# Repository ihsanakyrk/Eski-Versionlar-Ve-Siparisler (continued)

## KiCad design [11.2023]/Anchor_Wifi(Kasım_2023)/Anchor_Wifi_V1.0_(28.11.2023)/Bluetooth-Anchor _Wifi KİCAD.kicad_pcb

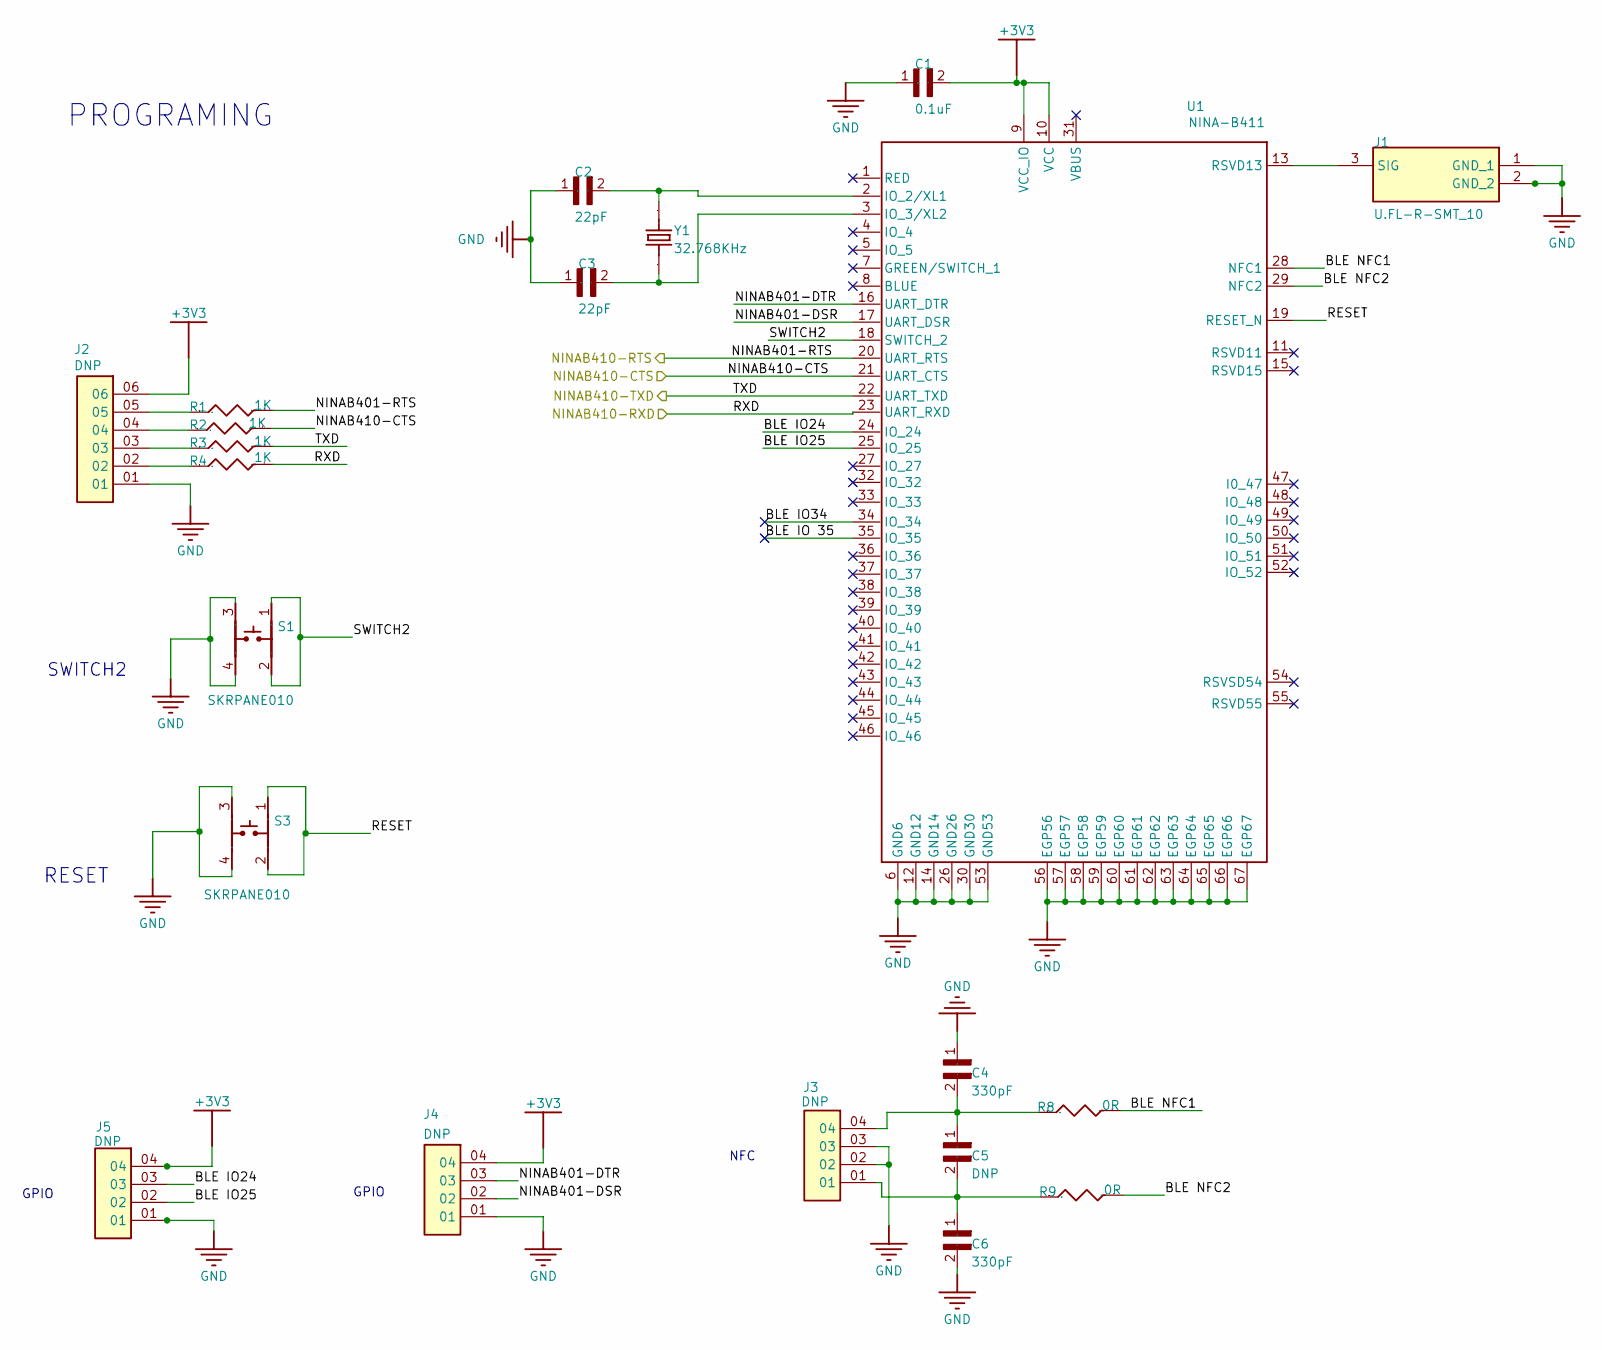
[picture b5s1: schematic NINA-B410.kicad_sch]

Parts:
C1: 0.1uF; C_0402
C2, C3: 22pF; C_0402
C4, C6: 330pF; C_0402
C5: DNP; C_0402
J1: U.FL-R-SMT_10; UFLRSMT10; MANUFACTURER_PART_NUMBER U.FL-R-SMT(10); MOUSER PART NUMBER 798-U.FL-R-SMT10
J2: DNP; Header_6Ways_2x54
J3, J4, J5: DNP; Header_4Ways_2x54_Male
R1, R2, R3, R4: 1K; Res_0402
R8, R9: 0R; Res_0402
S1, S3: SKRPANE010
U1: NINA-B411; NINA_LGA67R_1160X1000X223_PIN - duplicate
Y1: 32.768KHz; XTAL_ECS-3X8X

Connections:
+3V3: C1.2, J2.06, J4.04, J5.04, U1.9 (VCC_IO), U1.10 (VCC); also elsewhere on the board
BLE IO24: J5.03, U1.24 (IO_24)
BLE IO25: J5.02, U1.25 (IO_25)
BLE IO34: U1.34 (IO_34)
BLE IO 35: U1.35 (IO_35)
BLE NFC1: R8.2, U1.28 (NFC1)
BLE NFC2: R9.2, U1.29 (NFC2)
GND: C1.1, C2.1, C3.1, C4.1, C6.2, J1.1 (GND_1), J1.2 (GND_2), J2.01, J3.02, J3.03, J4.01, J5.01, S1.3, S1.4, S3.3, S3.4, U1.6 (GND6), U1.12 (GND12), U1.14 (GND14), U1.26 (GND26), U1.30 (GND30), U1.53 (GND53), U1.56 (EGP56), U1.57 (EGP57), U1.58 (EGP58), U1.59 (EGP59), U1.60 (EGP60), U1.61 (EGP61), U1.62 (EGP62), U1.63 (EGP63), U1.64 (EGP64), U1.65 (EGP65), U1.66 (EGP66), U1.67 (EGP67); also elsewhere on the board
NINAB401-DSR: J4.02, U1.17 (UART_DSR)
NINAB401-DTR: J4.03, U1.16 (UART_DTR)
NINAB401-RTS: R1.2, U1.20 (UART_RTS); also elsewhere on the board
NINAB410-CTS: R2.2, U1.21 (UART_CTS); also elsewhere on the board
NetC2_2: C2.2, U1.2 (IO_2/XL1), Y1.2
NetC3_2: C3.2, U1.3 (IO_3/XL2), Y1.1
NetC4_2: C4.2, C5.1, J3.04, R8.1
NetC6_1: C5.2, C6.1, J3.01, R9.1
NetJ1_3: J1.3 (SIG), U1.13 (RSVD13)
NetJ2_02: J2.02, R4.1
NetJ2_03: J2.03, R3.1
NetJ2_04: J2.04, R2.1
NetJ2_05: J2.05, R1.1
RESET: S3.1, S3.2, U1.19 (RESET_N)
RXD: R4.2, U1.23 (UART_RXD); also elsewhere on the board
SWITCH2: S1.1, S1.2, U1.18 (SWITCH_2)
TXD: R3.2, U1.22 (UART_TXD); also elsewhere on the board

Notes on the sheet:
GPIO
RESET
NFC
SWITCH2
PROGRAMING

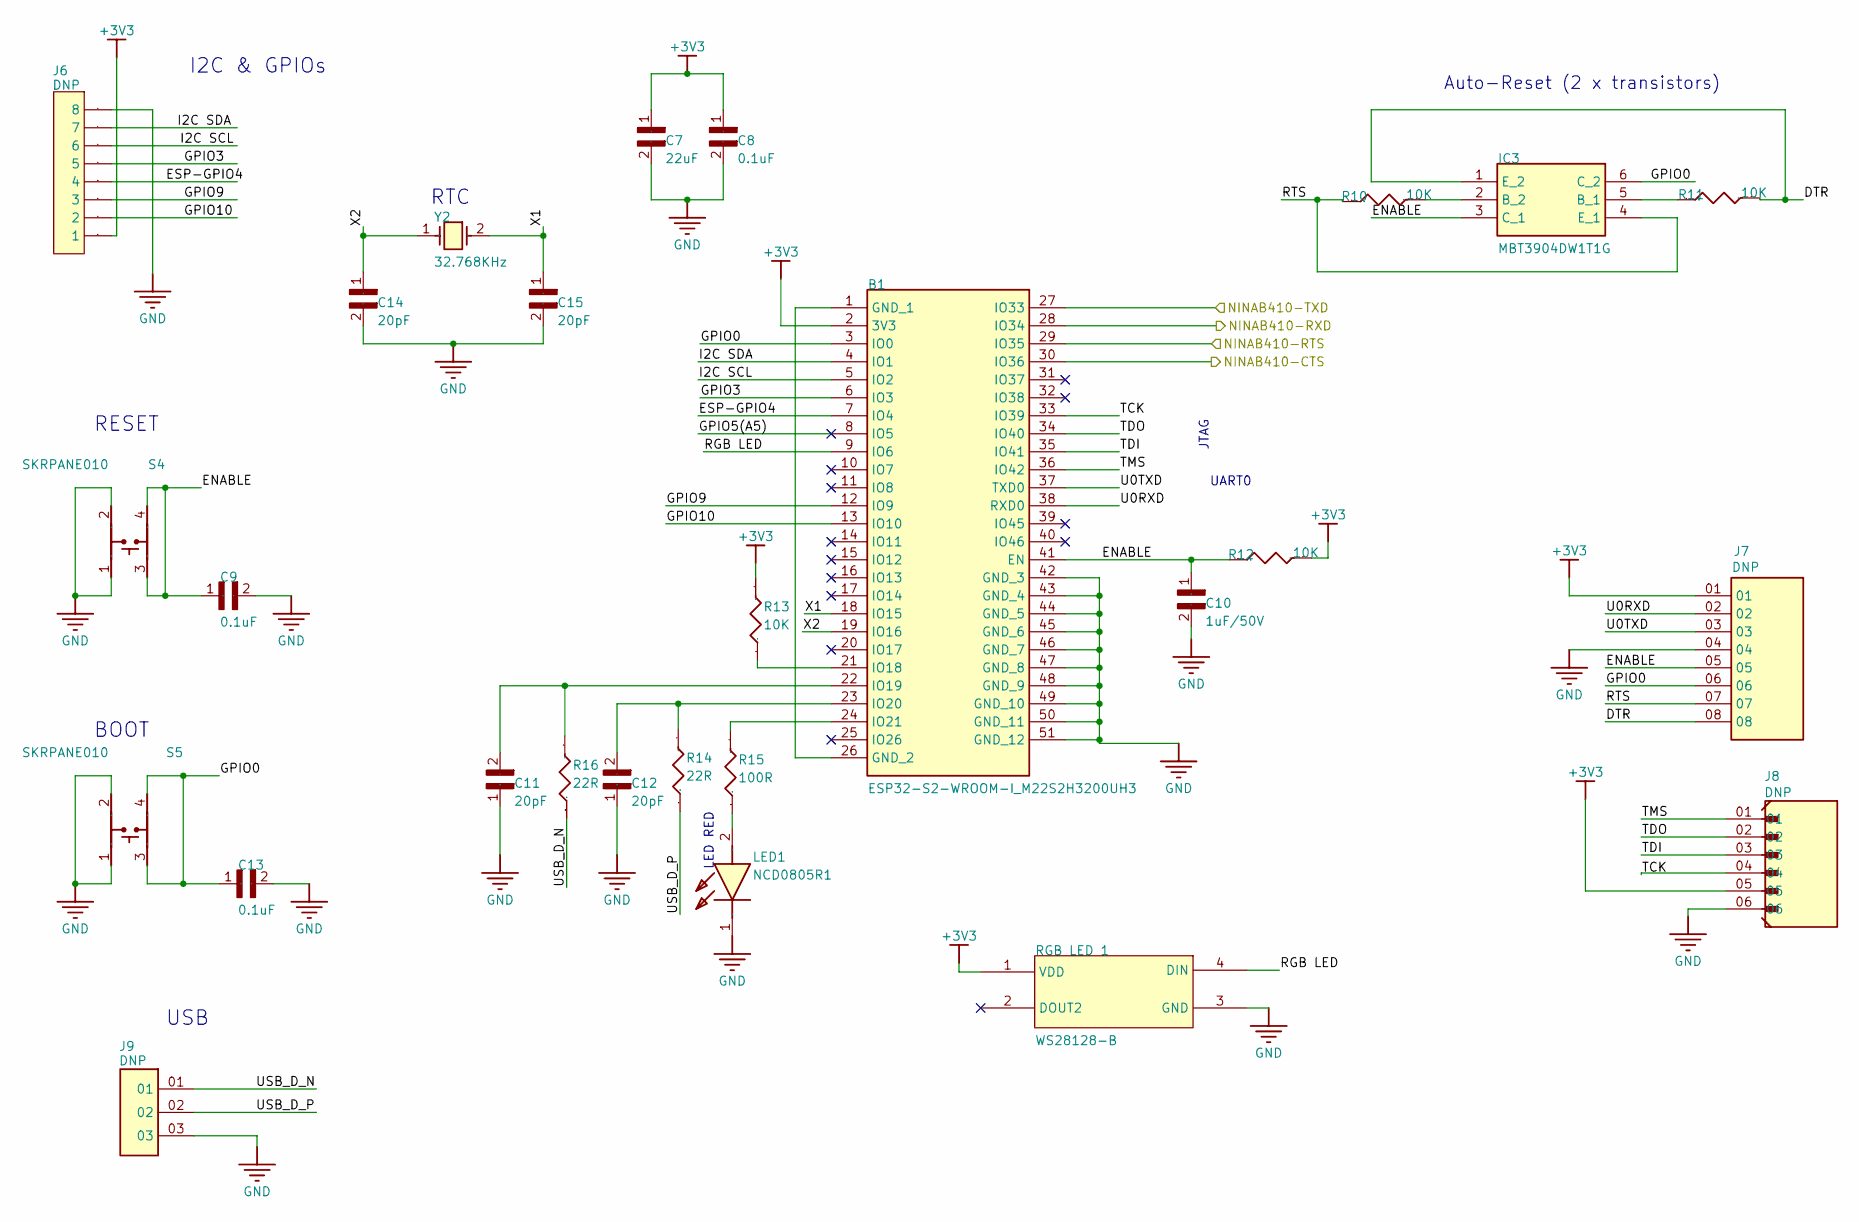
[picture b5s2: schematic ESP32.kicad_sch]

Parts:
B1: ESP32-S2-WROOM-I_M22S2H3200UH3; ESP32S2WROOMIM22S2H3200UH3Q0; MANUFACTURER_PART_NUMBER ESP32-S2-WROOM-I(M22S2H3200UH3Q0); MOUSER PART NUMBER 356-ESP32S2WRMI320UH
C7: 22uF; C_0402
C8, C9, C13: 0.1uF; C_0402
C10: 1uF/50V; C_0402
C11, C12, C14, C15: 20pF; C_0402
IC3: MBT3904DW1T1G; MANUFACTURER_PART_NUMBER MBT3904DW1T1G; MOUSER PART NUMBER 863-MBT3904DW1T1G
J6: DNP; Header_8ways_2x54
J7: DNP; 2x54 Header 8 pin
J8: DNP; Header_1x6_2_54
J9: DNP; Header_3Ways_2x54
LED1: NCD0805R1; MANUFACTURER_PART_NUMBER NCD0805R1; MOUSER PART NUMBER *
R10, R11, R12, R13: 10K; Res_0402
R14, R16: 22R; Res_0402
R15: 100R; Res_0402
RGB LED 1: WS28128-B
S4, S5: SKRPANE010
Y2: 32.768KHz; XTAL_ECS-3X8X

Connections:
+3V3: B1.2 (3V3), C7.1, C8.1, J6.1, J7.01, J8.05, R12.2, R13.2, RGB LED 1.1 (VDD); also elsewhere on the board
DTR: IC3.1 (E_2), J7.08, R11.2
ENABLE: B1.41 (EN), C9.1, C10.1, IC3.3 (C_1), J7.05, R12.1, S4.3, S4.4
ESP-GPIO4: B1.7 (IO4), J6.4
GND: B1.42 (GND_3), B1.43 (GND_4), B1.44 (GND_5), B1.45 (GND_6), B1.46 (GND_7), B1.47 (GND_8), B1.48 (GND_9), B1.49 (GND_10), B1.50 (GND_11), B1.51 (GND_12), C7.2, C8.2, C9.2, C10.2, C11.1, C12.1, C13.2, C14.2, C15.2, J6.8, J7.04, J8.06, J9.03, LED1.1 (K), RGB LED 1.3 (GND), S4.1, S4.2, S5.1, S5.2; also elsewhere on the board
GPIO0: B1.3 (IO0), C13.1, IC3.6 (C_2), J7.06, S5.3, S5.4
GPIO3: B1.6 (IO3), J6.5
GPIO5(A5): B1.8 (IO5)
GPIO9: B1.12 (IO9), J6.3
GPIO10: B1.13 (IO10), J6.2
I2C SCL: B1.5 (IO2), J6.6
I2C SDA: B1.4 (IO1), J6.7
NINAB401-RTS: B1.29 (IO35); also elsewhere on the board
NINAB410-CTS: B1.30 (IO36); also elsewhere on the board
NetB1_1: B1.1 (GND_1), B1.26 (GND_2)
NetB1_21: B1.21 (IO18), R13.1
NetB1_22: B1.22 (IO19), C11.2, R16.2
NetB1_23: B1.23 (IO20), C12.2, R14.2
NetB1_24: B1.24 (IO21), R15.2
NetD1_2: LED1.2 (A), R15.1
NetR10_2: IC3.2 (B_2), R10.2
NetR11_1: IC3.5 (B_1), R11.1
RGB LED: B1.9 (IO6), RGB LED 1.4 (DIN)
RTS: IC3.4 (E_1), J7.07, R10.1
RXD: B1.28 (IO34); also elsewhere on the board
TCK: B1.33 (IO39), J8.04
TDI: B1.35 (IO41), J8.03
TDO: B1.34 (IO40), J8.02
TMS: B1.36 (IO42), J8.01
TXD: B1.27 (IO33); also elsewhere on the board
U0RXD: B1.38 (RXD0), J7.02
U0TXD: B1.37 (TXD0), J7.03
USB_D_N: J9.01, R16.1
USB_D_P: J9.02, R14.1
X1: B1.18 (IO15), C15.1, Y2.2
X2: B1.19 (IO16), C14.1, Y2.1

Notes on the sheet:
RESET
USB
Auto-Reset (2 x transistors)
LED RED
UART0
RTC
I2C & GPIOs
JTAG
BOOT

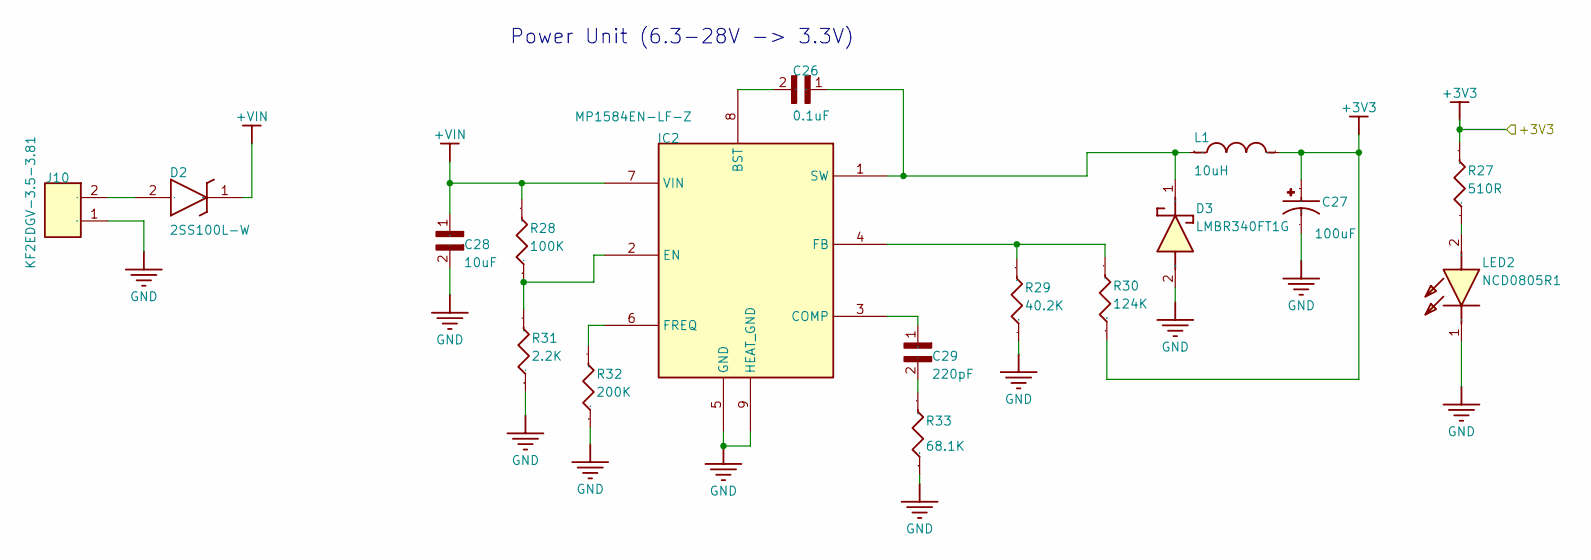
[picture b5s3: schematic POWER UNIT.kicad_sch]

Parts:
C26: 0.1uF; C_0402
C27: 100uF; XT100UF10V90RV0060
C28: 10uF; C_0402
C29: 220pF; C_0402
D2: 2SS100L-W; 2SS100LW; MANUFACTURER_PART_NUMBER 2SS100L-W; MOUSER PART NUMBER 583-2SS100L-W
D3: LMBR340FT1G; SODFL3618X143N; MANUFACTURER_PART_NUMBER SS34FA; MOUSER PART NUMBER 512-SS34FA
IC2: MP1584EN-LF-Z; SOIC127P600X170-9N
J10: KF2EDGV-3.5-3.81; SHDR2W80P0X381_1X2_862X700X920P
L1: 10uH; YSPI0530-100M
LED2: NCD0805R1; MANUFACTURER_PART_NUMBER NCD0805R1; MOUSER PART NUMBER *
R27: 510R; Res_0402
R28: 100K; Res_0402
R29: 40.2K; Res_0402
R30: 124K; Res_0402
R31: 2.2K; Res_0402
R32: 200K; Res_0402
R33: 68.1K; Res_0402

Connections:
+3V3: C27.1, L1.2, R27.2, R30.1; also elsewhere on the board
+VIN: C28.1, D2.1 (K), IC2.7 (VIN), R28.2
GND: C27.2, C28.2, D3.2 (A), IC2.5 (GND), IC2.9 (HEAT_GND), J10.1, LED2.1 (K), R29.1, R31.1, R32.1, R33.1; also elsewhere on the board
NetC26_1: C26.1, D3.1 (K), IC2.1 (SW), L1.1
NetC26_2: C26.2, IC2.8 (BST)
NetC29_1: C29.1, IC2.3 (COMP)
NetC29_2: C29.2, R33.2
NetD2_2: D2.2 (A), J10.2
NetD4_2: LED2.2 (A), R27.1
NetR28_1: IC2.2 (EN), R28.1, R31.2
NetR29_2: IC2.4 (FB), R29.2, R30.2
NetR32_2: IC2.6 (FREQ), R32.2

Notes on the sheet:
Power Unit (6.3-28V -> 3.3V)

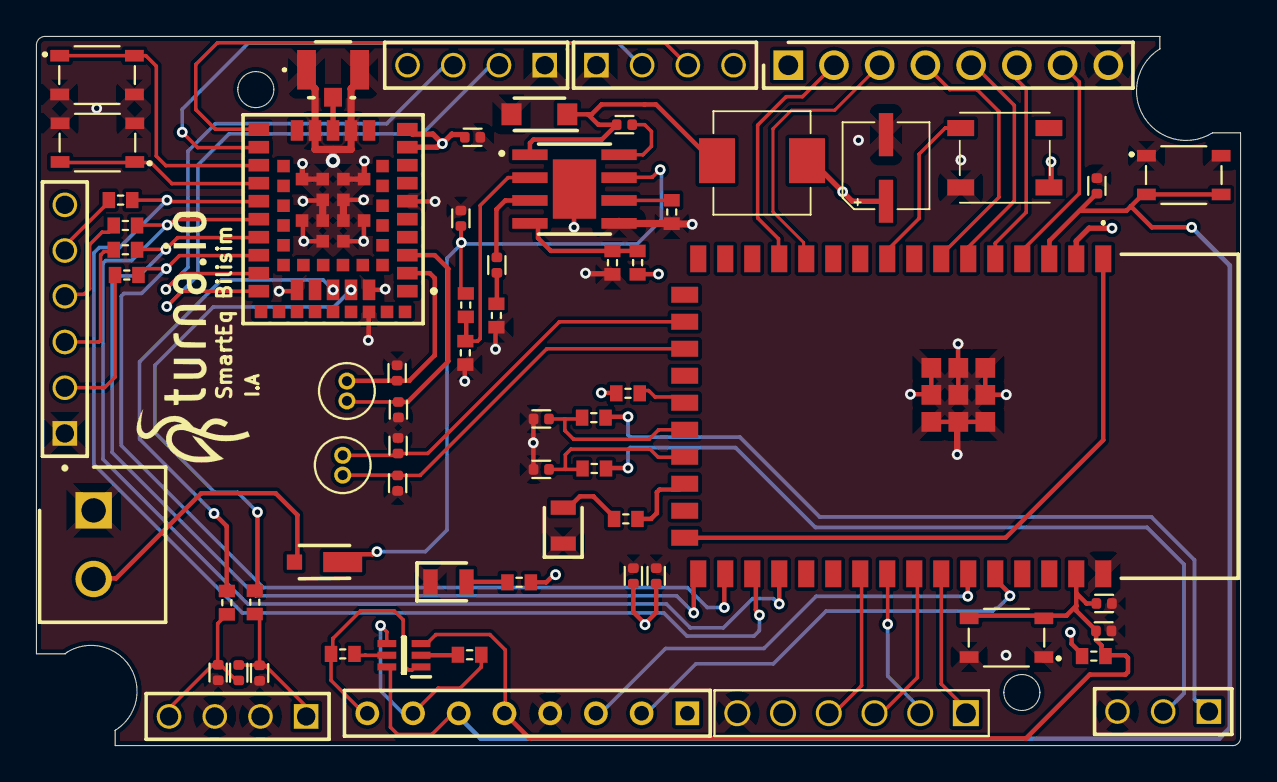
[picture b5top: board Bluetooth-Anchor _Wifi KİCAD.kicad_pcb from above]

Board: 4 copper layers, 66.9 x 39.4 mm, 65 parts (0 on the bottom side), 62 nets.
